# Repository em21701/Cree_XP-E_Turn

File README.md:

Cree_XP-E_Turn
=================

Cree XP-E Turn Board

This board fits 4 Cree XP-E LEDs into the board space of the EBAY Chinese flush mount turn signals.

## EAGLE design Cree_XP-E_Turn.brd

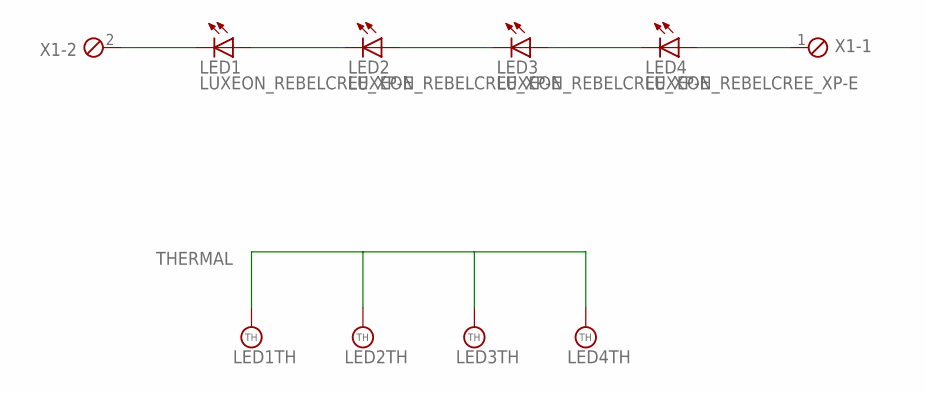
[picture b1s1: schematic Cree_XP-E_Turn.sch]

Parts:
LED1, LED2, LED3, LED4: LUXEON_REBELCREE_XP-E; CREE_XP-E
X1: MPT2; 2POL254

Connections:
unnamed: LED1.AN (A), LED2.CT (C)
unnamed: LED2.AN (A), LED3.CT (C)
unnamed: LED3.AN (A), LED4.CT (C)
THERMAL: LED1.TH, LED2.TH, LED3.TH, LED4.TH
V+: LED4.AN (A), X1.1
V-: LED1.CT (C), X1.2

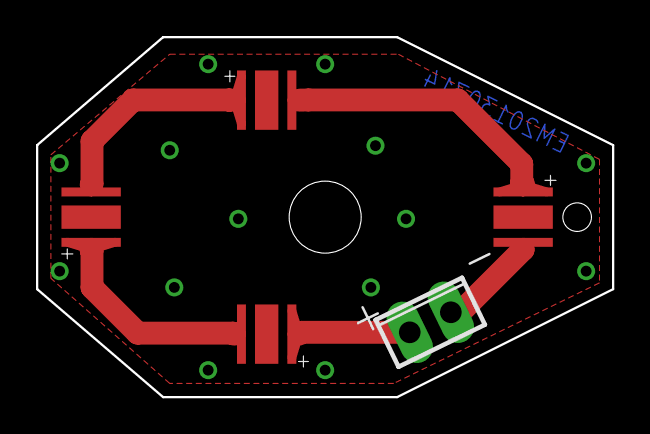
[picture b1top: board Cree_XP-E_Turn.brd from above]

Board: 2 copper layers, 32.0 x 20.0 mm, 5 parts (0 on the bottom side), 6 nets.

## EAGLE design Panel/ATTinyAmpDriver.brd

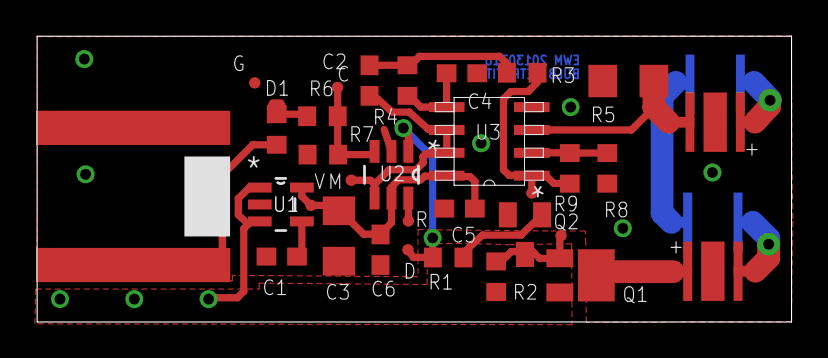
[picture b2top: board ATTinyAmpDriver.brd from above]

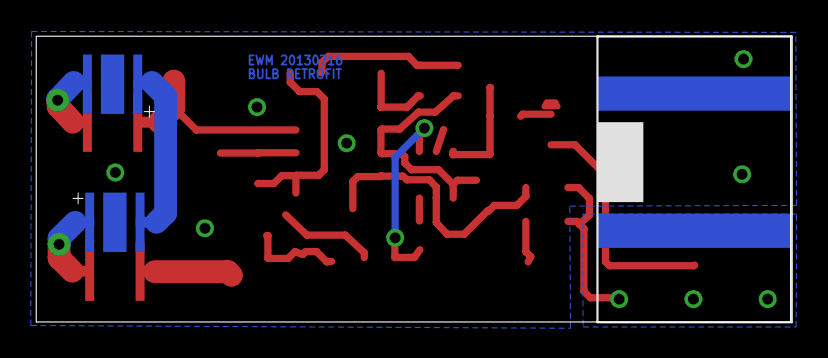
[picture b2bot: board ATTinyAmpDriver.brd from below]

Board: 2 copper layers, 41.9 x 15.9 mm, 34 parts (3 on the bottom side), 21 nets.

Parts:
+5V: TPI; TPI_PAD
C1: 10n; C0603
C2, C4, C5, C6: .1u; C0603
C3: 47u; C1206
D1: DIODE_0603; D0603
GND: TPI; TPI_PAD
LED1, LED2, LED3, LED4: LUXEON_REBELCREE_XP-E; CREE_XP-E
MEASURE: TPI; TPI_PAD
OUTA: TPI; TPI_PAD
PWM: TPI; TPI_PAD
Q1: SI2301CDS; SOT-23_POWER
Q2: BC846; SOT23
R1: 10k; R0603
R2, R7, R8: 1k; R0603
R3, R4: 3.9k; R0603
R5: .1; R1206
R6: 3.3k; R0603
R9: 28.7K; R0603
RESET: TPI; TPI_PAD
TPICLK: TPI; TPI_PAD
TPIDATA: TPI; TPI_PAD
U1: SPX5205M5-L-3-3; SOT95P280X145-5N
U2: ATTINY5-TSHR; SOT95P280X145-6N
U3: MCP6L2-X_SN; SOIC8-N_MC
U$1: CON_TAILLIGHT; TAILLIGHT

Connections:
+14V: Q1.P$2, R2.1, U1.1, U1.3, U$1.L1
BLINK: R6.1, R7.1, TPICLK.P$1, U2.3
CROSSOVER: LED2.CT, LED3.AN
D-: LED4.CT, R5.2, U3.3
GND: C1.2, C3.2, C4.2, C5.2, C6.2, GND.P$1, LED1.TH, LED2.TH, LED3.TH, LED4.TH, Q2.2, R5.1, R7.2, R8.2, U1.2, U2.2, U3.4, U$1.H2, U$1.L2
INA-: R8.1, R9.2, U3.2
INB+: C4.1, R4.2, U3.5
MEASURE: C2.1, MEASURE.P$1, U2.4, U3.6, U3.7
MOSFET: R1.1, TPIDATA.P$1, U2.1
unnamed: D1.1A, U$1.H1
unnamed: C1.1, U1.4
unnamed: LED1.AN, Q1.P$3
unnamed: D1.2C, R6.2
unnamed: PWM.P$1, Q1.P$1, Q2.3, R2.2
unnamed: Q2.1, R1.2
unnamed: LED1.CT, LED2.AN
unnamed: C2.2, R3.2, R4.1
unnamed: LED3.CT, LED4.AN
OUTA: OUTA.P$1, R3.1, R9.1, U3.1
RESET: RESET.P$1, U2.6
VCC: +5V.P$1, C3.1, C5.1, C6.1, U1.5, U2.5, U3.8

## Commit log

2013-07-15 Changed Readme and deleted leftover Luxeon files
2013-07-16 Used Updated XP-E footprint
2013-07-17 Turn and Tail combined Panel
2013-07-17 updated tail board in combined panel
